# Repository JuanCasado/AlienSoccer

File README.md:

# AlienSoccer

This project was made by a team of three students that I was part of at Complubot.

We built two robots that played soccer coordinately with a ball that emited infrared light.
The robots were able to detect the ball as well as recognize certain parts of the field like the white limitational lines on it that the robots couldn't cross. Also they detected the field's walls as well as each other using ultrasounds.
Both robots where identically built and the operated with the same software, anyway we had different game modes like goalkeeper or player to modify their behavior.

[View in prezi (Spanish)](https://prezi.com/view/UruUJdG32kYzkdQXmuUq "prezi")

## Main caracteristics
* **High modularity:** the robots had eight processors distributed along them, each one was in charge of a specific task, making every part of the robot independent of the others. We detected wich parts where connected to the robot and operate eith them. Also one independant part could make all its functionality without the others. This made much easier the building procces because we could work in multiple parts of the robot at the same time, also testing them was faster. If one part was damaged during a game we could replace it completely with a new one in less than a minute, also the same part could operate in any robot.
* **Friendly interface:** the robots had a set of buttons, a cirular array of leds and a speaker so at any moment we could be displaying whatever the robots were seeing by their sensors. Having a nice interface was critical mainly because it made testing much easier and faster.
* **Fast processing:** We had had eight Arduino processors distributed along each robot so we where doing hadrware parallelism at any time, the robots could reach a max cycle of sensor refresing of 50ms including processing the information, and decision making.

## Parts of the robots
* **Compass:** The robots could know where they were facing to target the enemy goal.
* **Ultrasounds:** The robots could measure distances of the walls and detect objects.
* **Ball sensor:** Each robot had a "donut" of sensor arroun it, the function of this "donut" was to determine the possition and distance of the ball.
* **UI:** thanks to a set of buttons, a speaker and a circular array of leds we could "talk" to the robot.
* **Floor sensors:** We had four arrays of six sensors each that could read the wite lines of the field.
* **Motors:** Along with the ball sensors this was one of the critical parts of the robot. The robots had for motor each disposed in an X form to make an omnidirectional platform. Each motor was ruled by one proccesor wich made PID control to the motor, the four motor processors were ruled by another one wich made PID control with the facing possition and the ball position and distance to decide the target velocities of the motors, the processors comunicated by i2c.
* **Main board:** we had an arduino Mega as master of all the other seven processors, here the robots made the most critical decissions.

[Mr.BlissfulGrin](http://www.mrblissfulgrin.com "mrblissfulgrin")

[Complubot](http://complubot.com/inicio/ "complubot")

## Promotional video
 
**Share the video with:** [https://youtu.be/aCtYLtXQVko](https://youtu.be/aCtYLtXQVko "https://youtu.be/aCtYLtXQVko")

## Fist tests

**Share the video with:** [https://youtu.be/rDMKiselTD4](https://youtu.be/rDMKiselTD4 "https://youtu.be/rDMKiselTD4")

## Images

Project done by Juan Casado Ballesteros

[Mr.BlissfulGrin](http://www.mrblissfulgrin.com "mrblissfulgrin")

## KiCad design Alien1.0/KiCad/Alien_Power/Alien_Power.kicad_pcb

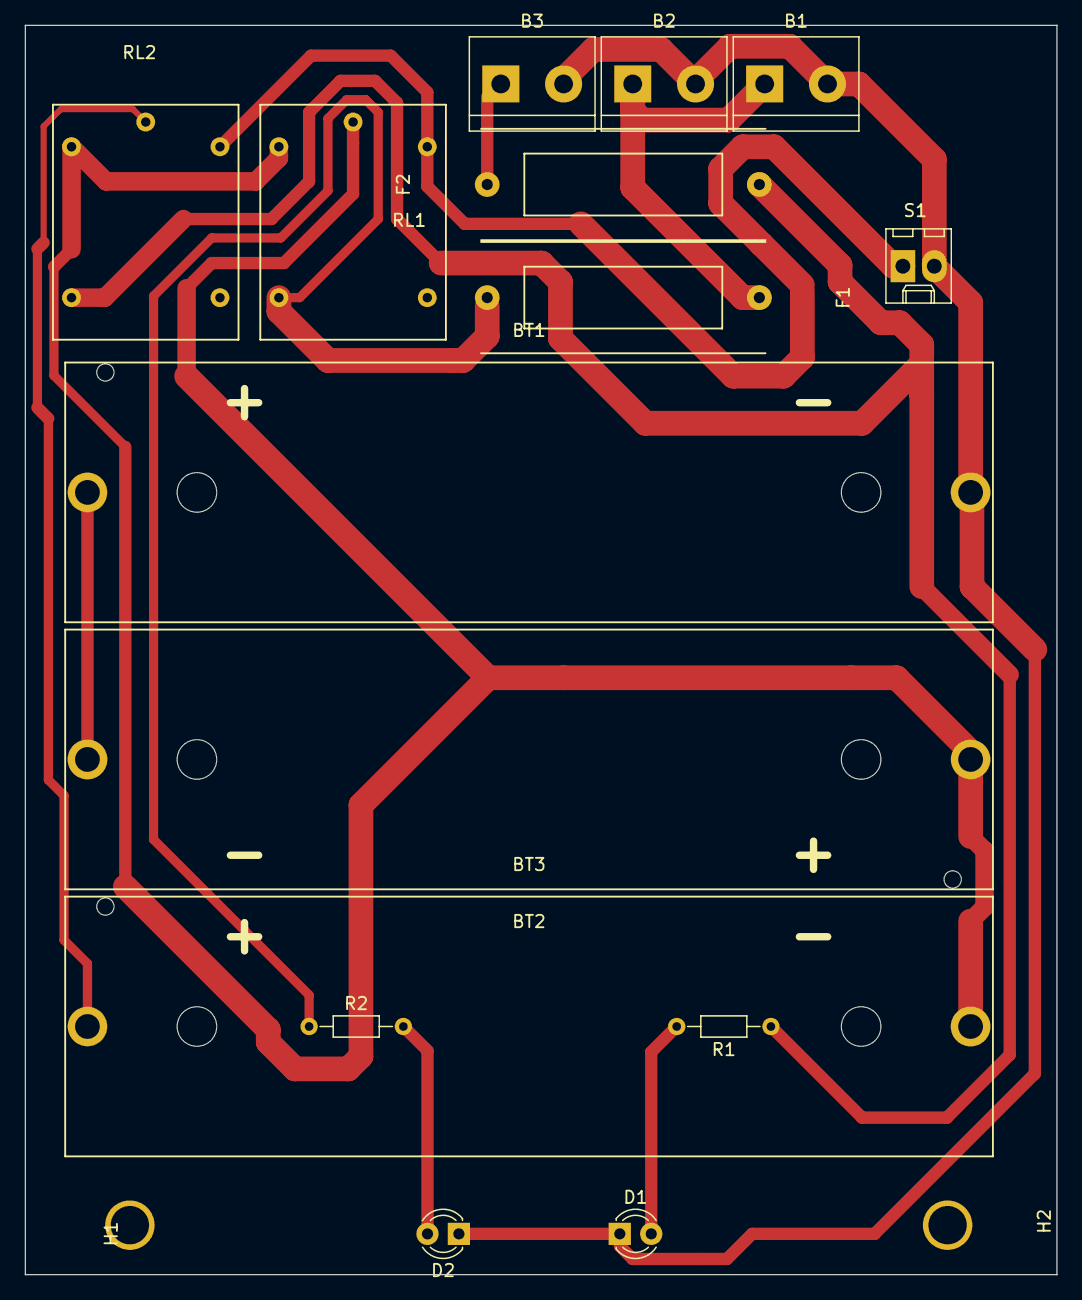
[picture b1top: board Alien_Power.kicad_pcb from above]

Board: 2 copper layers, 83.4 x 101.0 mm, 17 parts (0 on the bottom side), 11 nets.

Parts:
B1: BAT_ELEC_1; bornier2
B2: BAT_ELEC_2; bornier2
B3: BAT_POWER; bornier2
BT1: celda_1; Portapila
BT2: celda_2; Portapila
BT3: celda_3; Portapila
D1: RED_LED; LED_D3.0mm
D2: GREEN_LED; LED_D3.0mm
F1, F2: Fuse
H1: HOLE_1; Hole3mm
H2: HOLE_2; Hole3mm
R1, R2: 1K; R_Axial_DIN0204_L3.6mm_D1.6mm_P7.62mm_Horizontal
RL1, RL2: G5Q-1; Relay
S1: MAIN_SWITCH; Molex_KK-6410-02_02x2.54mm_Straight

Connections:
7.2v: BT2.1, BT3.2, RL1.2, RL1.5, RL2.5
10.8v: BT3.1, RL2.2
GND: B1.2, B2.2, B3.2, BT1.2, D1.1, D2.1, S1.2
unnamed: B1.1, B2.1, F1.1
unnamed: B3.1, F2.1
unnamed: BT1.1, BT2.2
unnamed: D1.2, R1.2
unnamed: D2.2, R2.2
unnamed: F1.2, R2.1, RL1.3
unnamed: F2.2, R1.1, RL2.3
SW1: RL1.1, RL2.1, S1.1

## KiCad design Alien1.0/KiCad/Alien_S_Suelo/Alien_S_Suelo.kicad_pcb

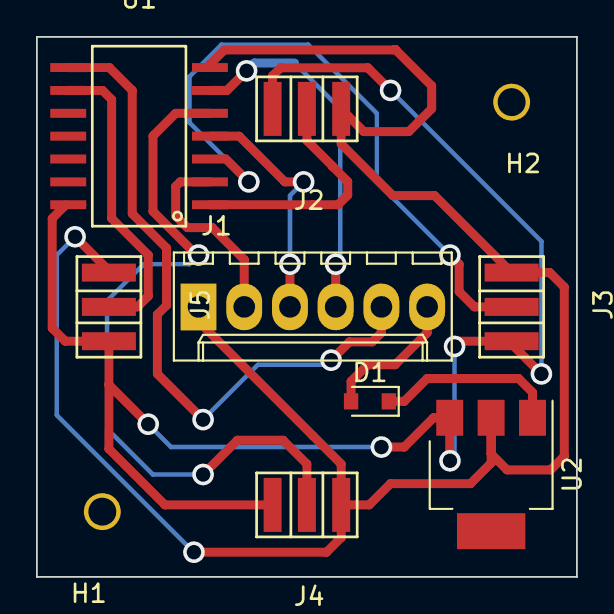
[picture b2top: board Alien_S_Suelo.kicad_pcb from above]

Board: 2 copper layers, 30.0 x 30.0 mm, 10 parts (0 on the bottom side), 12 nets.

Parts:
D1: D; D_0805
H1: HOLE_1; Hole3mm
H2: HOLE_2; Hole3mm
J1: C_SENSORES; Molex_KK-6410-06_06x2.54mm_Straight
J2: SENSOR_1; Con_soldado_3
J3: SENSOR_2; Con_soldado_3
J4: SENSOR_3; Con_soldado_3
J5: SENSOR_4; Con_soldado_3
U1: 74HC14; SO-14
U2: 7805; SOT-223

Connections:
+5V: J2.1, J3.1, J4.1, J5.1, U1.+5V, U2.VO
GND: J1.1, J2.3, J3.3, J4.3, J5.3, U1.GND, U2.GND
unnamed: D1.2, J1.6
SS_1: J2.2, U1.1
SS_2: J3.2, U1.3
SS_3: J4.2, U1.5
SS_4: J5.2, U1.9
S_1: J1.2, U1.2
S_2: J1.3, U1.4
S_3: J1.4, U1.6
S_4: J1.5, U1.8
VCC: D1.1, U2.VI

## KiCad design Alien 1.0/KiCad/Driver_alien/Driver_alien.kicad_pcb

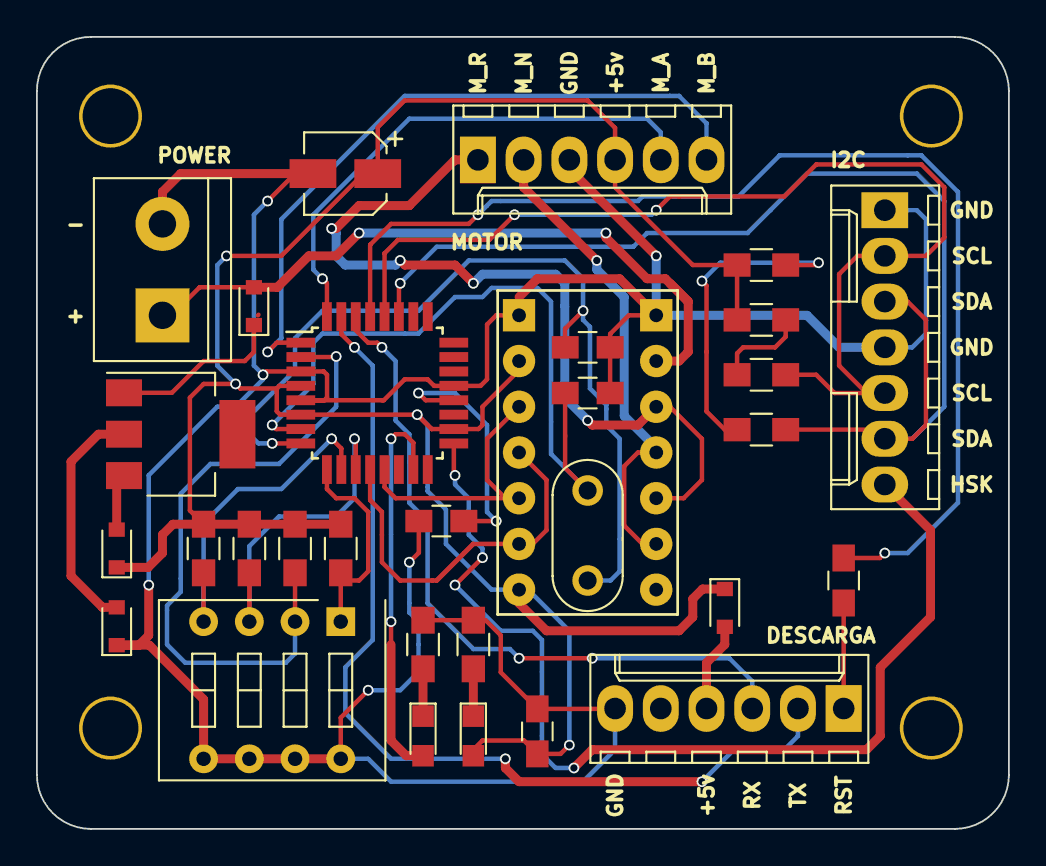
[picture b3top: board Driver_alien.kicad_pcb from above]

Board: 2 copper layers, 54.0 x 44.0 mm, 35 parts (0 on the bottom side), 32 nets.

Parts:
C1: 10uf; CP_Elec_4x5.3
C2, C5, C6: 100nf; C_0805_HandSoldering
C3, C4: 22pf; C_0805_HandSoldering
D1, D4, D5, D6: D; D_0805
D2, D3: LED; LED_0805
H1: hole1; Hole3mm
H2: hole2; Hole3mm
H3: hole3; Hole3mm
H4: hole4; Hole3mm
J1: Power; bornier2
J2: Con_motores; Molex_KK-6410-06_06x2.54mm_Straight
J3: Con_descarga; Molex_KK-6410-06_06x2.54mm_Straight
J4: Con_I2C; Molex_KK-6410-07_07x2.54mm_Straight
P1: JMP_2; R_0805_HandSoldering
P2: JMP_1; R_0805_HandSoldering
R1, R2, R3, R4: 10k; R_0805_HandSoldering
R5: 470; R_0805_HandSoldering
R6, R7: 2k2; R_0805_HandSoldering
R8: 220; R_0805_HandSoldering
SW_1: Selector_I2C; SW_DIP_x4_W7.62mm_Slide
U1: 7805; SOT-223
U2: DRV8835
U3: ATMEGA328P-AU; TQFP-32_7x7mm_Pitch0.8mm
Y1: Crystal; Resonator-2pin_w8.0mm_h3.5mm

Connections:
+5V: C1.1, C2.1, D3.2, D4.1, D6.1, J2.4, P1.1, P2.1, R1.1, R2.1, R3.1, R4.1, U2.2, U2.7, U3.4, U3.6, U3.18
ENABLE: U2.3, U2.5, U3.13
GND: C1.2, C2.2, C3.2, C4.2, C6.1, D5.1, J1.2, J2.3, J3.6, J4.1, J4.4, R5.1, R8.1, SW_1.5, SW_1.6, SW_1.7, SW_1.8, U2.1, U2.14, U3.3, U3.5, U3.21
HANDSHAKE: J4.7, U3.17
LED_1: D2.2, U3.15
M_A: J2.5, U3.32
M_B: J2.6, U3.1
M_NEGRO: J2.2, U2.9, U2.11
M_ROJO: J2.1, U2.10, U2.12
unnamed: C3.1, U3.8, Y1.1
unnamed: C4.1, U3.7, Y1.2
unnamed: C5.1, J3.1
unnamed: C6.2, U3.20
unnamed: D1.1, U1.VI
unnamed: D2.1, R5.2
unnamed: D3.1, R8.2
unnamed: D4.2, U1.VO
unnamed: D5.2, U1.GND
unnamed: D6.2, J3.4
unnamed: P1.2, R7.1
unnamed: P2.2, R6.1
PHASE: U2.4, U2.6, U3.12
RST: C5.2, U3.29
RX: J3.3, U3.30
SCL: J4.2, J4.5, R6.2, U3.28
SDA: J4.3, J4.6, R7.2, U3.27
SW1: R4.2, SW_1.1, U3.9
SW2: R3.2, SW_1.2, U3.2
SW3: R2.2, SW_1.3, U3.11
SW4: R1.2, SW_1.4, U3.10
TX: J3.2, U3.31
VCC: D1.2, J1.1, U2.13

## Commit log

2018-08-17 SUMMER 2018
2018-08-17 Create LICENSE
2018-08-18 Imperdibles video
2018-08-18 Complubot logo
2018-08-18 Rename
2018-08-20 videos
